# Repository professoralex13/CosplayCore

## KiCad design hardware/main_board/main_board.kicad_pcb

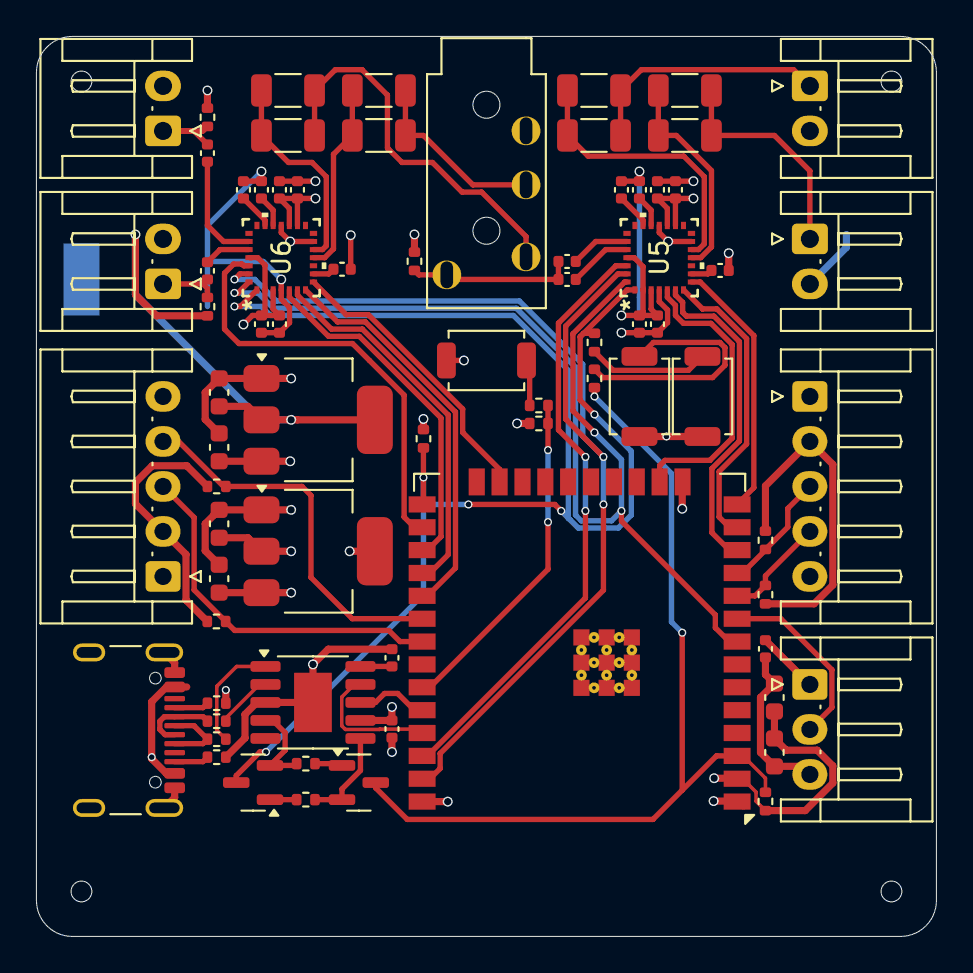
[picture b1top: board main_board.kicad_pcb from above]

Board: 4 copper layers, 50.0 x 50.0 mm, 79 parts (1 on the bottom side), 62 nets.

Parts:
C1, C39: 10u; C_0603_1608Metric
C3, C40: 22u; C_0603_1608Metric
C4, C5, C6, C12, C15, C25, C28: 100n; C_0402_1005Metric
C9: 100n; C_0603_1608Metric
C10: 1u; C_0603_1608Metric
C13, C14, C17, C18, C26, C27, C30, C31: 100u; C_1206_3216Metric
C16, C19, C20, C22, C23, C29, C32, C33, C35, C36: 4.7u; C_0402_1005Metric
C21, C24, C34, C37: 1u; C_0402_1005Metric
H2, H3, H4, H5: ToolingHole; ToolingHole_1.152mm
J1: USB Port; USB_C_Receptacle_GCT_USB4105-xx-A_16P_TopMnt_Horizontal
J2, J8: I2C; JST_EH_S5B-EH_1x05_P2.50mm_Horizontal
J3: LED; JST_EH_S3B-EH_1x03_P2.50mm_Horizontal
J4: Left_Mic; JST_EH_S2B-EH_1x02_P2.50mm_Horizontal
J5: Left_Speaker; JST_EH_S2B-EH_1x02_P2.50mm_Horizontal
J6: Right_Mic; JST_EH_S2B-EH_1x02_P2.50mm_Horizontal
J7: Right_Speaker; JST_EH_S2B-EH_1x02_P2.50mm_Horizontal
NT2: NetTie_2; NetTie-2_SMD_Pad2.0mm
Q1, Q2: MMBT3904; SOT-23
R1, R2: 22; R_0402_1005Metric
R3, R4, R12, R15, R16, R17: 5.1k; R_0402_1005Metric
R5, R6, R8, R9, R10, R13, R14: 10k; R_0402_1005Metric
R7: 51k; R_0402_1005Metric
R11, R18, R19: 1k; R_0402_1005Metric
SW1, SW2, SW3: SW_Push; SW_SPST_TS-1088-xR020
U1, U7: AMS1117-3.3; SOT-223-3_TabPin2
U2: CH340K; SSOP-10-1EP_3.9x4.9mm_P1mm_EP2.1x3.3mm
U4: Headphone Jack; PJ-320A
U5, U6: WM8988LGECN/V; QFN28_4X4_CIR
U8: ESP32-WROOM-32E

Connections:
+3V3A: C22.2, C23.2, C35.2, C36.2, C40.2, R8.2, R9.1, R10.2, U5.16 (HPVDD), U5.17 (AVDD), U6.16 (HPVDD), U6.17 (AVDD), U7.2 (VO)
+3V3D: C3.2, C5.2, C9.2, C10.1, C12.2, C15.2, C25.2, C28.2, J2.2, J8.2, R7.2, R12.1, R13.2, R14.2, R15.2, R16.1, R17.2, U1.2 (VO), U2.7 (VCC), U5.2 (DCVDD), U5.3 (DBVDD), U5.25 (MODE), U6.2 (DCVDD), U6.3 (DBVDD), U6.25 (MODE), U8.2 (VDD)
+5V: C1.2, C4.1, C39.2, J1.A4 (VBUS), J1.A9 (VBUS), J1.B4 (VBUS), J1.B9 (VBUS), J2.1, J3.1, J8.1, U1.3 (VI), U7.3 (VI)
/DTR: Q2.2 (E), R5.1, U2.4 (~DTR)
/Ext->Int_CLK: U6.5 (BCLK), U8.27 (IO16)
/Ext->Int_In: U6.6 (DACDAT), U8.28 (IO17)
/Ext->Int_LRC: U6.7 (LRC), U8.29 (IO5)
/Ext->Int_Out: U6.8 (ADCDAT), U8.23 (IO15)
/Ext->Int_Select: U6.26 (CSB), U8.26 (IO4)
/GPIO0: Q2.3 (C), R14.1, R18.2, U5.1 (MCLK), U6.1 (MCLK), U8.25 (IO0)
/Gen_Button: R7.1, R11.2, U8.33 (IO21)
/Headset_Left: C30.1, C31.1, U4.2 (Tip)
/Headset_Mic: C21.1, C24.1, R9.2, U4.1 (Sleeve)
/Headset_Right: C26.1, C27.1, U4.3 (Ring1)
/Int->Ext_CLK: U5.5 (BCLK), U8.16 (IO13)
/Int->Ext_In: U5.6 (DACDAT), U8.12 (IO27)
/Int->Ext_LRC: U5.7 (LRC), U8.13 (IO14)
/Int->Ext_Out: U5.8 (ADCDAT), U8.14 (IO12)
/Int->Ext_Select: U5.26 (CSB), U8.36 (IO22)
/LED_Data: J3.2, U8.9 (IO33)
/MCU_EN: Q1.3 (C), R13.1, R19.2, U8.3 (EN)
/MOSI: U5.27 (SDIN), U6.27 (SDIN), U8.37 (IO23)
/Mic_Left: C34.1, J4.1, R8.1
/Mic_Right: C37.1, J6.1, R10.1
/Out_CLK1: J2.4, R16.2, U8.30 (IO18)
/Out_CLK2: J8.4, R12.2, U8.10 (IO25)
/Out_DAT1: J2.3, R17.1, U8.31 (IO19)
/Out_DAT2: J8.3, R15.1, U8.11 (IO26)
/Prog_RX: U2.8 (TXD), U8.34 (RXD0/IO3)
/Prog_TX: U2.9 (RXD), U8.35 (TXD0/IO1)
/RTS: Q1.2 (E), R6.1, U2.6 (~RTS)
/SPI_CLK: U5.28 (SCLK), U6.28 (SCLK), U8.8 (IO32)
/Speaker_Left: C17.1, C18.1, J5.1
/Speaker_Right: C13.1, C14.1, J7.1
/USB_D+: R2.2, U2.1 (UD+)
/USB_D-: R1.2, U2.2 (UD-)
GND: C1.1, C3.1, C4.2, C5.1, C6.2, C9.1, C10.2, C12.1, C15.1, C19.1, C20.1, C25.1, C28.1, C32.1, C33.1, C39.1, C40.1, J1.A1 (GND), J1.A12 (GND), J1.B1 (GND), J1.B12 (GND), J1.S1 (SHIELD), J2.5, J3.3, J8.5, NT2.1, R3.2, R4.2, SW1.1, SW2.1, SW3.1, U1.1 (GND), U2.3 (GND), U2.11 (GND), U5.4 (DGND), U6.4 (DGND), U7.1 (GND), U8.1 (GND), U8.15 (GND), U8.38 (GND), U8.39 (GND)
GNDA: C16.2, C22.1, C23.1, C29.2, C35.1, C36.1, J4.2, J5.2, J6.2, J7.2, NT2.2, U4.4 (Ring2), U5.13 (HPGND), U5.18 (AGND), U6.13 (HPGND), U6.18 (AGND)
unnamed: J1.A5 (CC1), R3.1
unnamed: J1.B5 (CC2), R4.1
unnamed: J1.A6 (D+), J1.B6 (D+), R2.1
unnamed: J1.A7 (D-), J1.B7 (D-), R1.1
unnamed: Q1.1 (B), R5.2
unnamed: Q2.1 (B), R6.2
unnamed: R11.1, SW3.2
unnamed: R18.1, SW1.2
unnamed: R19.1, SW2.2
unnamed: C6.1, U2.10 (V3)
unnamed: C16.1, U5.9 (HPCOM)
unnamed: C21.2, U5.24 (LINPUT1)
unnamed: C17.2, C18.2, U5.12 (LOUT1)
unnamed: C24.2, U5.23 (RINPUT1)
unnamed: C13.2, C14.2, U5.11 (ROUT1)
unnamed: C19.2, U5.20 (VMID)
unnamed: C20.2, U5.19 (VREF)
unnamed: C29.1, U6.9 (HPCOM)
unnamed: C34.2, U6.24 (LINPUT1)
unnamed: C30.2, C31.2, U6.12 (LOUT1)
unnamed: C37.2, U6.23 (RINPUT1)
unnamed: C26.2, C27.2, U6.11 (ROUT1)
unnamed: C32.2, U6.20 (VMID)
unnamed: C33.2, U6.19 (VREF)

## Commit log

2026-01-05 format properly
2026-01-05 refactor: split up bluetooth
2026-01-06 fix: auto adjust i2s frequency from a2dp sink
2026-01-06 setup basic serial bluetooth comms
2026-01-10 feat: basic android flutter app
2026-01-11 feat: app volume control and digital filtering through loopback
2026-01-12 fix: unconnected traces
2026-01-12 feat: basic double codec operation
2026-02-06 start rust
2026-02-06 feat: working spi
2026-02-06 format
2026-02-06 refactor: split spi files
2026-02-10 feat: mic boost
2026-02-15 switch to esp-idf-hal
2026-02-15 feat: i2s
2026-02-15 config: enable bluetooth
2026-02-15 feat: bluetooth audio
2026-02-16 extract bluetooth and i2s to seperate threads
